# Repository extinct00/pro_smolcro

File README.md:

# pro_smolcro
Some requirements for this board:
1) Should be a replacement for a pro micro, therefore have the same pinout and should have the same dimensions
2) Have a 5V out from the usb that could be used to either power the other microcontroller or to power some 5v LEDs for better efficiency
3) RP2040 based board with 16MB of flash memory
4) Look into how to detect VUSB from QMK, so i can make sure it works

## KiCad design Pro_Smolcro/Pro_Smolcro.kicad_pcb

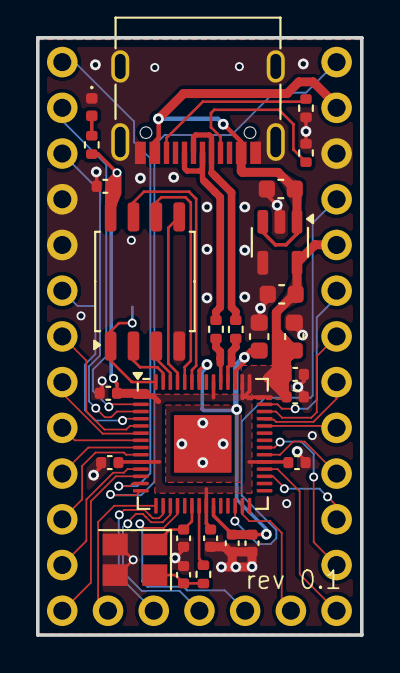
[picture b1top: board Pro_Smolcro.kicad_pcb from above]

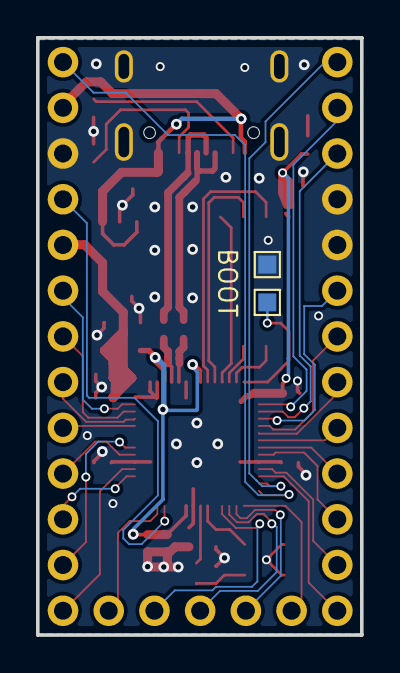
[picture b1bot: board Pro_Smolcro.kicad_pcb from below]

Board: 2 copper layers, 18.0 x 33.2 mm, 32 parts (2 on the bottom side), 46 nets.

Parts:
C1, C2, C11, C12: 1u; C_0603_1608Metric
C3, C4, C5, C6, C7, C8, C9, C10, C13: 100n; C_0402_1005Metric
C14, C15: 15p; C_0402_1005Metric
D4: LED; LED_0402_1005Metric
J1: SHOU HAN TYPE-C 16PIN 2MD(073); USB_C_Receptacle_G-Switch_GT-USB-7010ASV
J2: Conn_01x05; PinSocket_1x05_P2.54mm_Vertical
J3, J4: Conn_01x13; PinSocket_1x13_P2.54mm_Vertical
R1, R2: 5.1k; R_0402_1005Metric
R3, R4: 27.4; R_0402_1005Metric
R7: 1k; R_0402_1005Metric
R8: 68R; R_0402_1005Metric
TP4, TP5: TestPoint; TestPoint_Pad_1.0x1.0mm
U1: RP2040; QFN-56-1EP_7x7mm_P0.4mm_EP3.2x3.2mm
U3: W25Q128JVS; SOIC-8_5.3x5.3mm_P1.27mm
U4: TLV75733PDBV; SOT-23-5
Y1: ABM8-272-T3; Crystal_SMD_3225-4Pin_3.2x2.5mm

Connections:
3V3: C2.1, C3.1, C4.1, C5.1, C6.1, C7.1, C8.1, C12.1, C13.1, J4.5, R8.1, U1.1 (IOVDD), U1.10 (IOVDD), U1.22 (IOVDD), U1.33 (IOVDD), U1.42 (IOVDD), U1.43 (ADC_AVDD), U1.44 (VREG_IN), U1.48 (USB_VDD), U1.49 (IOVDD), U3.8 (VCC), U4.5 (OUT)
5V: C1.1, J1.A4 (VBUS), J1.A9 (VBUS), J1.B4 (VBUS), J1.B9 (VBUS), J4.2, U4.1 (IN), U4.3 (EN)
+1V1: C9.1, C10.1, C11.1, U1.23 (DVDD), U1.45 (VREG_VOUT), U1.50 (DVDD)
CLK: U1.52 (QSPI_SCLK), U3.6 (CLK)
CS: TP4.1, U1.56 (QSPI_SS), U3.1 (~CS)
D0: U1.53 (QSPI_SD0), U3.5 (DI/IO_{0})
D1: U1.55 (QSPI_SD1), U3.2 (DO/IO_{1})
D2: U1.54 (QSPI_SD2), U3.3 (~WP/IO_{2})
D3: U1.51 (QSPI_SD3), U3.7 (~HOLD/~RESET/IO_{3})
D_N: J1.A7 (D-), J1.B7 (D-), R4.1
D_P: J1.A6 (D+), J1.B6 (D+), R3.1
GND: C1.2, C2.2, C3.2, C4.2, C5.2, C6.2, C7.2, C8.2, C9.2, C10.2, C11.2, C12.2, C13.2, C14.2, C15.2, D4.1 (K), J1.A1 (GND), J1.A12 (GND), J1.B1 (GND), J1.B12 (GND), J1.S1 (SHIELD), J3.4, J3.5, J4.3, R1.2, R2.2, TP5.1, U1.19 (TESTEN), U1.57 (GND), U3.4 (GND), U4.2 (GND), U4.4 (GNDNC), Y1.2, Y1.3
GP0: J3.2, U1.2 (GPIO0)
GP1: J3.3, U1.3 (GPIO1)
GP2: J3.6, U1.4 (GPIO2)
GP3: J3.7, U1.5 (GPIO3)
GP4: J3.8, U1.6 (GPIO4)
GP5: J3.9, U1.7 (GPIO5)
GP6: J3.10, U1.8 (GPIO6)
GP7: J3.11, U1.9 (GPIO7)
GP8: J3.12, U1.11 (GPIO8)
GP9: J3.13, U1.12 (GPIO9)
GP10: J3.1, U1.13 (GPIO10)
GP11: J4.1, U1.14 (GPIO11)
GP12: J2.1, U1.15 (GPIO12)
GP13: J2.2, U1.16 (GPIO13)
GP14: J2.3, U1.17 (GPIO14)
GP15: J2.4, U1.18 (GPIO15)
GP16: J2.5, U1.27 (GPIO16)
GP20: J4.11, U1.31 (GPIO20)
GP21: J4.13, U1.32 (GPIO21)
GP22: J4.10, U1.34 (GPIO22)
GP23: J4.12, U1.35 (GPIO23)
GP26: J4.9, U1.38 (GPIO26_ADC0)
GP27: J4.8, U1.39 (GPIO27_ADC1)
GP28: J4.7, U1.40 (GPIO28_ADC2)
GP29: J4.6, U1.41 (GPIO29_ADC3)
unnamed: C15.1, R7.2, Y1.4
unnamed: D4.2 (A), R8.2
unnamed: J1.A5 (CC1), R1.1
unnamed: J1.B5 (CC2), R2.1
RST: J4.4, U1.26 (RUN)
USBN: R4.2, U1.46 (USB_DM)
USBP: R3.2, U1.47 (USB_DP)
XIN: C14.1, U1.20 (XIN), Y1.1
XOUT: R7.1, U1.21 (XOUT)

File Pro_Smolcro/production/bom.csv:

Designator,Footprint,Quantity,Value,LCSC Part #
"C1, C11, C12, C2",0603,4,1u,
"C10, C13, C3, C4, C5, C6, C7, C8, C9",0402,9,100n,
"C14, C15",0402,2,15p,C86285
D4,0402,1,LED,C130719
J1,USB_C_Receptacle_G-Switch_GT-USB-7010ASV,1,SHOU HAN TYPE-C 16PIN 2MD(073),C2765186
J2,PinSocket_1x05_P2.54mm_Vertical,1,Conn_01x05,
"J3, J4",PinSocket_1x13_P2.54mm_Vertical,2,Conn_01x13,
"R1, R2",0402,2,5.1k,
"R3, R4",0402,2,27.4,C2759791
R7,0402,1,1k,
R8,0402,1,68R,C2909380
"TP4, TP5",TestPoint_Pad_1.0x1.0mm,2,TestPoint,
U1,QFN-56-1EP_7x7mm_P0.4mm_EP3.2x3.2mm,1,RP2040,C2040
U3,SOIC-8_5.3x5.3mm_P1.27mm,1,W25Q128JVS,C97521
U4,SOT-23-5,1,TLV75733PDBV,C485517
Y1,Crystal_SMD_3225-4Pin_3.2x2.5mm,1,ABM8-272-T3,C20625731

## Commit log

2025-03-08 started schematic
2025-03-11 finished layout of the main components
2025-03-12 finished the layout
2025-03-12 exported gerbers, no panel still tho
